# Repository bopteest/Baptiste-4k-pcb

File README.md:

# Baptiste-4k-pcb
Overview
This repository contains the PCB design files for a 4-key keyboard implemented using KiCad. The project was undertaken to gain proficiency in KiCad and serve as a stepping stone for more complex commissioned and personal projects. This simple yet functional 4-key keyboard is a great starting point for anyone looking to enhance their skills in PCB design and KiCad.

.

Features
-Compact 4-key layout for simplicity and ease of understanding.

-Utilizes MX switch design for a reliable and customizable key feel.

-Integrated with a Mega32 microcontroller, programmable using QMK firmware.

-Designed using KiCad, a powerful and open-source PCB design software.

-Minimalist design to focus on core concepts for beginners.

.

Exploring the Design

The schematic files (*.sch) and the PCB layout files (*.kicad_pcb) as well as all gerber files can be located in the 4k Folder.
Component footprints and symbols are stored in the footprints and symbols folders, respectively.

.

Customization

Feel free to modify and customize the design to suit your preferences or use it as a starting point for more complex projects. You can experiment with different key layouts, add more keys, or integrate additional features.

.

Contributing

Contributions are welcome! If you find any issues or have suggestions for improvements, please open an issue or create a pull request.

.

Contact

If you have any questions or feedback, feel free to reach out to baptiste.lavielle@gmail.com

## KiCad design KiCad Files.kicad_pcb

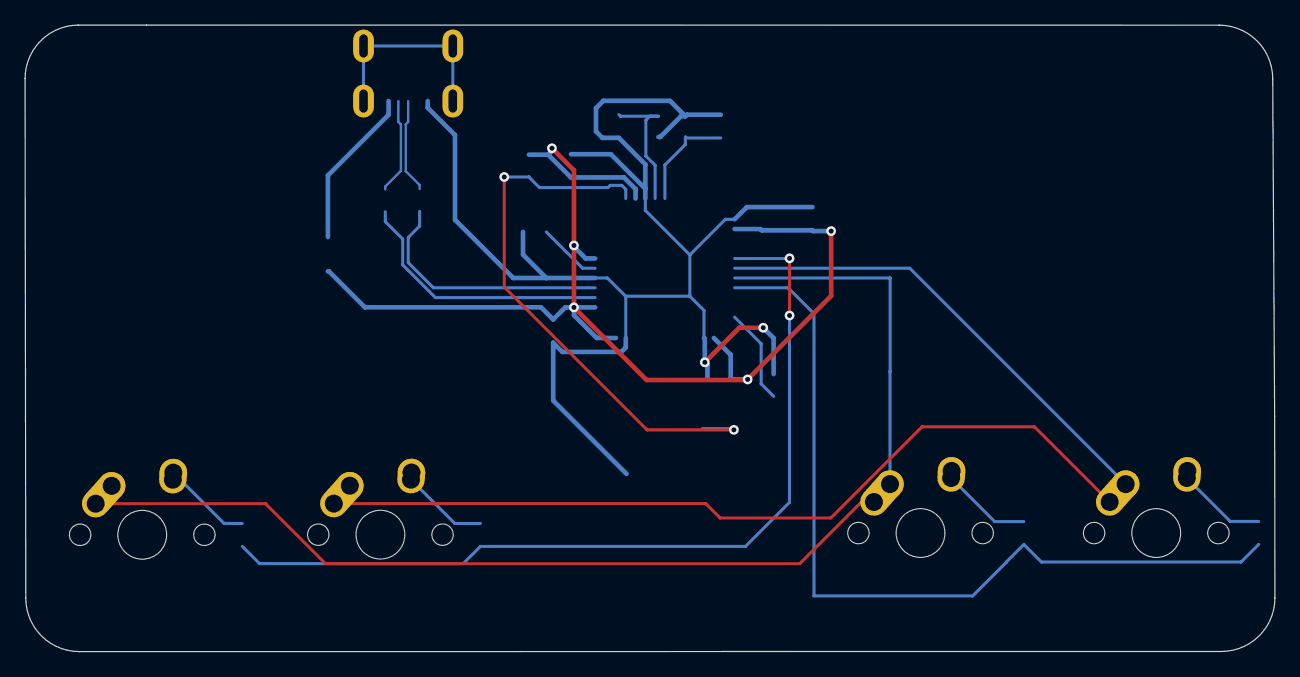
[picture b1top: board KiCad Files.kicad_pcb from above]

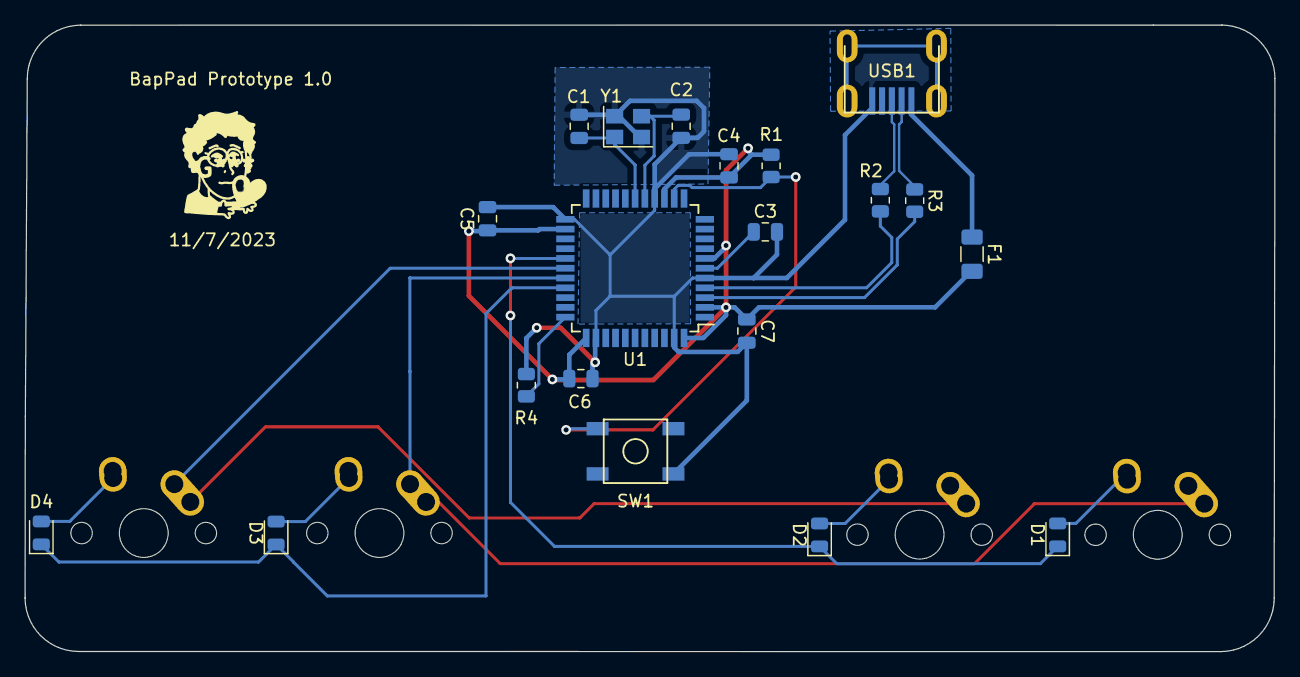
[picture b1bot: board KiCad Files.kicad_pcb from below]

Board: 2 copper layers, 102.2 x 51.2 mm, 24 parts (20 on the bottom side), 20 nets.

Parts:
C1, C2: 22pF; C_0805_2012Metric
C3: 1uF; C_0805_2012Metric
C4, C5, C6: 0.1uF; C_0805_2012Metric
C7: 10uF; C_0805_2012Metric
D1, D2, D3, D4: SOD-123; D_0805_2012Metric
F1: 500mA; Fuse_1206_3216Metric
MX1, MX2, MX3, MX4: MX-NoLED; MX-1U-NoLED
R1, R4: 10k; R_0805_2012Metric
R2, R3: 22; R_0805_2012Metric
SW1: SW_Push; SKQG-1155865
U1: ATmega32U4-A; TQFP-44_10x10mm_P0.8mm
USB1: Molex-0548190589
Y1: 16MHz; Crystal_SMD_3225-4Pin_3.2x2.5mm

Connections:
+5V: C4.1, C5.1, C6.1, C7.1, F1.2, R1.1, U1.2 (UVCC), U1.7 (VBUS), U1.14 (VCC), U1.24 (AVCC), U1.34 (VCC), U1.44 (AVCC)
COL0: MX1.1 (COL), MX3.1 (COL), U1.29 (PB5)
COL1: MX2.1 (COL), MX4.1 (COL), U1.28 (PB4)
D+: R2.1, USB1.3 (D+)
D-: R3.1, USB1.4 (D-)
GND: C1.1, C2.1, C3.2, C4.2, C5.2, C6.2, C7.2, R4.2, SW1.1, U1.5 (UGND), U1.15 (GND), U1.23 (GND), U1.35 (GND), U1.43 (GND), USB1.1 (GND), Y1.2, Y1.4
unnamed: D1.2 (A), MX1.2 (ROW)
unnamed: D2.2 (A), MX2.2 (ROW)
unnamed: D3.2 (A), MX3.2 (ROW)
unnamed: D4.2 (A), MX4.2 (ROW)
unnamed: R2.2, U1.4 (D+)
unnamed: R3.2, U1.3 (D-)
unnamed: C3.1, U1.6 (UCAP)
unnamed: C1.2, U1.17 (XTAL1), Y1.1
unnamed: C2.2, U1.16 (XTAL2), Y1.3
unnamed: R4.1, U1.33 (~HWB/PE2)
unnamed: R1.2, SW1.2, U1.13 (~RESET)
ROW0: D1.1 (K), D2.1 (K), U1.27 (PD7)
ROW1: D3.1 (K), D4.1 (K), U1.30 (PB6)
VCC: F1.1, USB1.5 (VBUS)

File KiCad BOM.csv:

"Id";"Designator";"Footprint";"Quantity";"Designation";"Supplier and ref";
1;"MX4,MX2,MX3,MX1";"MX-1U-NoLED";4;"MX-NoLED";;;
2;"D4,D3,D1,D2";"D_0805_2012Metric";4;"SOD-123";;;
3;"R4,R1";"R_0805_2012Metric";2;"10k";;;
4;"SW1";"SKQG-1155865";1;"SW_Push";;;
5;"C3";"C_0805_2012Metric";1;"1uF";;;
6;"U1";"TQFP-44_10x10mm_P0.8mm";1;"ATmega32U4-A";;;
7;"C4,C6,C5";"C_0805_2012Metric";3;"0.1uF";;;
8;"R3,R2";"R_0805_2012Metric";2;"22";;;
9;"USB1";"Molex-0548190589";1;"Molex-0548190589";;;
10;"F1";"Fuse_1206_3216Metric";1;"500mA";;;
11;"C7";"C_0805_2012Metric";1;"10uF";;;
12;"C2,C1";"C_0805_2012Metric";2;"22pF";;;
13;"Y1";"Crystal_SMD_3225-4Pin_3.2x2.5mm";1;"16MHz";;;

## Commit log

2023-03-10 Initialize Project
2023-03-10 Add submodules
2023-03-10 Add footprint libraries
    PCB Specific Library for schematic and pcb
2023-03-10 Add Schematic and Footprint Bindings
2023-11-02 Final Changes to schematic
    Made some final touches to the schematic before beginning the PCB
2023-11-02 PCB Implimented
    Set up the PCB, now just needs to be organized and traced accordingly.
2023-11-03 PCB Outline.
    Outlined the PCB, with organized components, rounded edges, and beginning to trace
2023-11-07 Minimizing Tracing
    To try and minimize or organize the tracing, I decided to practice an experiments with different routing ideas and concepts
2023-11-08 Finalized Tracing
    Finished Optimizing tracing, and began running through errors.
2023-11-14 Finished Design, including Gerber Files
    Here are the gerber files
2023-11-15 BOM and Fab Placements
